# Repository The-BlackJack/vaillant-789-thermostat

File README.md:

# Vaillant 7-8-9 Smart-Home-Thermostat für Home Assistant (ESPHome)

**Smart Home für alte Vaillant-Thermen:** Ein selbst gebautes WLAN-Wandthermostat
für **Vaillant-Gasthermen ohne eBUS**. Die Heizung erscheint in **Home Assistant**
als ganz normales Thermostat, mit Raumtemperatur, Zeitplänen, Automationen,
App-Steuerung und Sprachassistent. Vor Ort gibt es ein E-Paper-Display und einen
Drehknopf. Das Thermostat
ersetzt den alten Raumregler (hier einen **calorMATIC 332**) an seinem Platz an
der Wand. Die Therme wird stufenlos über die analoge **7-8-9-Schnittstelle**
gesteuert, eingebunden ist alles per **ESPHome in Home Assistant**.

*English summary:* A DIY room thermostat for Vaillant gas boilers with the analog
7-8-9 interface (no eBUS). An ESP32-C3 drives terminal 7 through an optocoupler,
RC filter and op-amp; supply comes from terminal 8. It has an e-paper display,
a rotary encoder and an SHT3x/SHT4x sensor, runs ESPHome with PID room control,
and integrates with Home Assistant. KiCad files, Gerbers, a perfboard layout,
3D-printable enclosure (OpenSCAD) and firmware are included. Documentation is in German.

> [!WARNING]
> **Nachbau auf eigene Gefahr.** Du arbeitest an einer Gasheizung. Die
> 7-8-9-Klemmen führen Kleinspannung (ca. 24 V), trotzdem gilt:
> - Die Therme vorher stromlos schalten.
> - Nur die Klemmen des Raumreglers anfassen.
> - Bei Unsicherheit eine Fachkraft fragen.
>
> Ein Fehler in der Steuerung kann die Heizung abschalten oder heißer laufen
> lassen. Der Drehknopf an der Therme bleibt in jedem Fall die obere Grenze.
> **Projektstand:** Schaltung, Platine und Firmware sind entworfen und
> geprüft (ERC/DRC fehlerfrei, Firmware-YAML syntaktisch geprüft), aber
> **noch nicht als fertiges Gerät im Betrieb getestet.** Erfahrungen und
> Korrekturen sind willkommen (Issues / Pull Requests).

---

## Inhalt

- [Wie funktioniert die 7-8-9-Schnittstelle?](#wie-funktioniert-die-7-8-9-schnittstelle)
- [Schaltung](#schaltung)
- [Funktionen der Firmware](#funktionen-der-firmware)
- [Drei Hardware-Varianten](#drei-hardware-varianten)
- [Teile](#teile)
- [Gehäuse (3D-Druck)](#gehäuse-3d-druck)
- [Aufbau und Inbetriebnahme](#aufbau-und-inbetriebnahme)
- [Kalibrierung](#kalibrierung)
- [Ordnerstruktur](#ordnerstruktur)
- [Offene Punkte](#offene-punkte)
- [Lizenz](#lizenz)

---

## Wie funktioniert die 7-8-9-Schnittstelle?

Ältere Vaillant-Thermen (hier eine **atmoTEC VCW 194/3-C-HL**) haben drei
Klemmen für einen stetigen Raumregler:

| Klemme | Bedeutung |
| --- | --- |
| **7** | Stellsignal: Spannung bestimmt die Vorlauf-Solltemperatur |
| **8** | Versorgung für den Regler (ca. 24 V) |
| **9** | Masse |

Der Regler **zieht Klemme 7 herunter**. Je niedriger die Spannung, desto
niedriger die Vorlauftemperatur. Unter etwa 10 V ist die Heizung aus. Die Therme
nimmt immer das **Minimum** aus Klemme 7 und ihrem eigenen Drehknopf, der Knopf
ist also eine harte Obergrenze.

An meiner Therme gemessen:

| Messung | Wert |
| --- | --- |
| Klemme 8 gegen 9 | 23,6 V (unter 24 mA Last kein relevanter Abfall) |
| Klemme 7 offen (kein Regler) | 22 V |
| Klemme 7, keine Wärmeanforderung | 10,1 V |
| Klemme 7, volle Anforderung | 17,8 V → 82 °C Vorlauf (Drehknopf voll auf) |

Andere Thermen können abweichen. Deshalb gibt es in der Firmware eine
[Kalibrierung](#kalibrierung).

## Schaltung

Schaltplan als PDF: [pcb-tht/fertigung/schaltplan.pdf](pcb-tht/fertigung/schaltplan.pdf)

```
VERSORGUNG (aus Klemme 8, Masse = Klemme 9 = ESP-GND)
  Kl.8 ─►|─ D1 1N5819 ─┬─ +V (ca. 23 V) ─ C1 100µF ─ GND
                       ├─ U2 78L09 ─ +9V  (C3 am Eingang, C4 100n am Ausgang)
                       └─ R7 100Ω ─┬─ C7 220µF ─ GND
                                   └─ U4 TRACO TSR 0.5-2450 ─┬─ C8 1000µF ─ GND
                                                             └─ ESP32-C3 SuperMini „5V“
STEUERUNG KLEMME 7 (fail-safe: ESP aus → Opto aus → +9 V am Tiefpass → Klemme 7 frei)
  GPIO3 ─ R1 330Ω ─ PC817 (Anode)            PC817 Kathode, Emitter ─ GND
  PC817 Kollektor ─ R2 10k ─ +9V
  PC817 Kollektor ─ R3 100k ─┬─ LM358 IN+
                             └─ C5 4,7µF X7R (kein Elko) ─ GND
  LM358 IN− ─ R4 100k ─ GND,  IN− ─ R5 120k ─ OUT   → Verstärkung 2,2
  Kl.7 ─ R6 220Ω ─►|─ LM358 OUT   (D2 1N4148, Kathode zum OPV)
```

- **PWM und Optokoppler:** Der ESP erzeugt ein PWM-Signal (500 Hz). Der
  Optokoppler zieht damit einen 9-V-Pegel taktweise auf Masse.
- **Glättung:** Der RC-Tiefpass macht daraus eine Gleichspannung von 0–9 V.
- **OPV:** Er verstärkt diese Spannung mit Faktor 2,2 auf 0–19,8 V und zieht
  Klemme 7 über die Diode auf diesen Wert herunter. Hochziehen kann er die
  Klemme nicht.
- **Fail-safe:** Fällt der ESP aus, sperrt der Optokoppler. Klemme 7 bleibt dann
  bei etwa 20 V, und die Therme heizt nach ihrem eigenen Drehknopf.
- **Arbeitsbereich:** 10,1–17,8 V an Klemme 7 entsprechen etwa 48–87 % PWM.
  Im Mittel braucht die Schaltung 12–15 mA aus Klemme 8.

**Peripherie (3,3 V vom ESP):**

| Teil | Anschlüsse |
| --- | --- |
| E-Paper Waveshare 2,9" V2 | DIN GPIO6, CLK GPIO4, CS GPIO7, DC GPIO5, RST GPIO10, BUSY GPIO1 |
| Sensor SHT31-D (oder SHT40) | SDA GPIO8, SCL GPIO9 |
| Drehgeber EC11 mit Taster | A GPIO21, B GPIO20, Taster GPIO0 |

## Funktionen der Firmware

Datei: [vaillant-789.yaml](vaillant-789.yaml) (ESPHome, ESP-IDF)

- **PID-Raumregelung:** In Home Assistant erscheint ein normales Thermostat.
  Der Wärmebedarf (0–100 %) wird auf einen einstellbaren Vorlaufbereich
  umgerechnet.
- **Betriebsarten:**
  - Aus
  - Raumregelung
  - Vorlauf manuell
  - Kalibrierung (PWM-Pegel direkt vorgeben)
- **Notbetrieb:** Fällt der Raumsensor aus, wird eine feste Vorlauftemperatur gefahren.
- **E-Paper-Anzeige:**
  - Raumtemperatur und Soll-Wert
  - Vorlauf-Soll und Wärmebedarf (bei „Vorlauf manuell“ und Kalibrierung
    stattdessen der tatsächliche PWM-Pegel)
  - Status und WLAN

  Simulation der Anzeige in sechs Zuständen, erzeugt mit
  [tools/display_sim.py](tools/display_sim.py) (gleiche Koordinaten und
  Schriften wie in der YAML, prüft Überstände).
- **Drehgeber:**
  - Drehen: Soll-Temperatur in 0,5-°C-Schritten
  - Drücken: Heizung ein/aus
- **Kalibrierung über Home Assistant:**
  - Spannung bei 50 % / 85 % PWM
  - Kennlinie Vorlauf ↔ Spannung (zwei Punkte)
  - Temperatur-Offset

Für eigene Zugangsdaten [secrets.example.yaml](secrets.example.yaml) nach
`secrets.yaml` kopieren und ausfüllen. Den Sensor-Typ (SHT31-D: `sht3xd`,
SHT40: `sht4x`) passt du in der YAML an.

## Drei Hardware-Varianten

Die Schaltung ist in allen drei Varianten gleich. Du kannst dir aussuchen, wie
du sie aufbaust.

| Variante | Ordner | Beschreibung |
| --- | --- | --- |
| **A – Platine zum Selbstlöten (empfohlen)** | [`pcb-tht/`](pcb-tht/) | Nur die Leiterplatte bei JLCPCB o. ä. fertigen lassen (Gerber-ZIP liegt bei). Alle Bauteile bedrahtet, nur zwei Kondensatoren als SMD 1210 mit Handlöt-Pads. |
| B – Platine mit SMD-Bestückung | [`pcb/`](pcb/) | Komplett bei JLCPCB bestückt (BOM/CPL im JLCPCB-Format). Bequemer, aber deutlich teurer. |
| C – Lochraster | [`lochraster/`](lochraster/) | 70 × 50 mm Lochrasterplatine mit Bestückungs- und Verdrahtungsplan. Ein Skript prüft alle Verbindungen. |

| THT-Platine (oben) | SMD-Variante | Lochraster (Lötseite) |
| --- | --- | --- |
|  |  |  |

**Zu allen Platinen:**
- **Format:** 70 × 50 mm, 2 Lagen.
- **Anschluss Therme:** Schraubklemme 7-8-9 am rechten Rand.
- **ESP:** Der ESP32-C3 SuperMini steckt in zwei Buchsenleisten, mit der Antenne nach oben über einer kupferfreien Zone.
- **Erzeugung:** Die KiCad-Projekte werden per Python-Skript aus einer
  gemeinsamen Netzliste erzeugt (`tools/design.py`), inklusive eines kleinen
  eigenen Autorouters. Du kannst die Dateien aber auch ganz normal in KiCad 10
  öffnen und bearbeiten.

## Teile

Alle Teile sind bei **Reichelt** erhältlich, der ESP32-C3 SuperMini zum
Beispiel bei Blinkyparts oder AliExpress. Stückliste mit Artikelnummern und
Links: [lochraster/README.md → Einkaufsliste](lochraster/README.md#einkaufsliste).
Für Variante A brauchst du die Lochrasterplatine und den Silberdraht daraus nicht.

Kosten (Stand Ende 2026): etwa 55 € bei Reichelt, davon rund 40 € für Display,
Sensor und Drehgeber. Dazu kommen ca. 5 € für den ESP und ein paar Euro für 5
Leiterplatten.

## Gehäuse (3D-Druck)

- **Modell:** Parametrisch in OpenSCAD:
  [vaillant-789-gehaeuse.scad](vaillant-789-gehaeuse.scad), 150 × 100 × 36 mm.
  Fertige STLs liegen in [`druck/`](druck/):
  - Rückplatte, wird an die Wand geschraubt (Langlöcher an den Positionen der alten calorMATIC-Halterung)
  - Frontgehäuse mit Displayfenster, belüfteter Sensorkammer und Lüftung oben
  - Drehknopf für die EC11-Achse (rund mit Schlitz oder D-Achse, umschaltbar)
- **Verschraubung:** ruthex-Gewindeeinsätze,
  M2 für die Platine und M3 für Front und Rückplatte. Die Maße sind oben in der
  `.scad` als Parameter einstellbar.
- **Material:** PETG oder ASA. PLA wird an der Wand in Heizungsnähe weich.
  Gute Werte sind 0,2 mm Schichthöhe, 3 Wände und 20 % Füllung.
- **Passform:** Die Platine ist mit den hohen Bauteilen gegen das Gehäuse
  geprüft ([Seitenansicht](druck/passform-seite.png)).
- **Maße:** Siehe [gehaeuse-massbild.png](gehaeuse-massbild.png). Wer eine
  andere Halterung hat, ändert `screw_ur` und `screw_ll` in der `.scad`.

## Aufbau und Inbetriebnahme

1. **Platine bestücken:** Die Hinweise zur Einbaurichtung stehen in
   [pcb-tht/README.md](pcb-tht/README.md) bzw. [lochraster/README.md](lochraster/README.md).
2. **Ohne Therme testen:** Etwa 24 V an Klemme 8/9 anlegen (Labornetzteil, Strom
   auf 100 mA begrenzen) und die Spannungen messen:
   - **+V:** ca. 23 V
   - **+9V:** 9 V
   - **5V am ESP:** 5 V
3. **ESP flashen:** `vaillant-789.yaml` im ESPHome Device Builder kompilieren
   und per USB flashen. Danach geht es auch per OTA.
4. **Ausgang prüfen, noch ohne Therme:** Klemme 7 über einen Widerstand von
   etwa 10 kΩ an 22 V hängen. In der Betriebsart „Pegel manuell“ die Spannung
   an Klemme 7 bei verschiedenen PWM-Pegeln messen.
5. **An die Therme anschließen:** Therme stromlos schalten, den alten Regler
   abklemmen und 7-8-9 an die Schraubklemme anschließen.

## Kalibrierung

Alle Werte stellst du in Home Assistant ein. Sie werden dauerhaft gespeichert.

1. **PWM-Kennlinie:** Betriebsart „Pegel manuell (Kalibrierung)“ wählen. PWM
   auf 50 % und auf 85 % stellen und jeweils die Spannung an Klemme 7 messen.
   Die Werte trägst du unter „Spannung bei Pegel 50 %/85 %“ ein.
2. **Vorlauf-Kennlinie:** Betriebsart „Vorlauf manuell“ wählen. Für einen
   niedrigen und einen hohen Vorlauf jeweils die Spannung und den Vorlauf an der
   Therme ablesen und als unteren und oberen Kennlinienpunkt eintragen.
3. **„Heizung aus“:** Die Spannung, bei der die Therme sicher aus ist, etwa
   0,5 V unter der gemessenen Schwelle.
4. **Temperatur-Offset:** Gleicht die Eigenerwärmung im Gehäuse aus. Dazu mit
   einem Referenzthermometer vergleichen.

## Ordnerstruktur

```
vaillant-789.yaml             ESPHome-Firmware
secrets.example.yaml          Vorlage für die Zugangsdaten
vaillant-789-gehaeuse.scad    Gehäuse (OpenSCAD)
druck/                        STL-Dateien und Ansichten
gehaeuse-massbild.png         Maßbild Gehäuse
display-sim.png               Simulation der E-Paper-Anzeige
tools/display_sim.py          erzeugt display-sim.png aus dem Display-Code
pcb-tht/                      Variante A: KiCad-Projekt THT, Gerber, Renders, Generator-Skripte
pcb/                          Variante B: KiCad-Projekt SMD (JLCPCB-Bestückung), BOM/CPL
lochraster/                   Variante C: Lochraster-Layout, Verdrahtungsliste, Einkaufsliste
Einkaufsliste.md              Bestellliste für Variante B
```

## Offene Punkte

- **ESP-Reihenabstand:** Den Abstand der beiden Pinreihen des ESP32-C3
  SuperMini (15,24 mm angenommen) am eigenen Modul nachmessen. Es gibt Klone mit
  abweichendem Abstand.
- **Firmware:** Kompiliert mit ESPHome 2026.11.0 und auf einem ESP32-C3
  SuperMini getestet (WLAN, Home-Assistant-API). Display, Sensor und Drehgeber
  sind noch nicht angeschlossen; offen sind `model: 2.90inv2` vs.
  `2.90inv2-r2` beim Display und `resolution` beim Drehgeber.
- **WLAN beim SuperMini:** Viele Module verbinden sich bei voller
  Sendeleistung nicht („Auth Expired“). Die YAML setzt deshalb
  `output_power: 8.5dB`.
- **Kalibrierung:** Der untere Kennlinienpunkt (ca. 35 °C) muss am fertigen
  Gerät bestimmt werden.
- **Display-Höhe:** Den Abstand zwischen Display-Rückseite und dem höchsten
  Elko (ca. 4 mm) am echten Display prüfen.

## Lizenz

[MIT](LICENSE). Nutzung, Nachbau und Änderung sind ausdrücklich erwünscht. Die
KiCad-Bibliotheksteile unterliegen der KiCad-Bibliothekslizenz (CC-BY-SA 4.0
mit Ausnahme für erzeugte Platinen).

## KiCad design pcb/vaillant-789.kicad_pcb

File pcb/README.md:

# Platine Vaillant 7-8-9 Thermostat (KiCad 10)

70 × 50 mm, 2 Lagen, 1,6 mm, 4 × M2-Löcher im Raster 65 × 45 mm.
ERC und DRC (mit Schaltplan-Parität) laufen ohne Fehler und Warnungen durch.

## Bestellen bei JLCPCB

1. `fertigung/vaillant-789-gerber.zip` hochladen (2 Lagen, 1,6 mm, HASL, Farbe nach Wunsch).
2. „PCB Assembly“ → **Top Side** → `fertigung/BOM-JLCPCB.csv` und `fertigung/CPL-JLCPCB.csv`.
3. **In der Bestückungsvorschau jedes Teil auf Lage und Polarität prüfen.** Die
   Drehwinkel stammen direkt aus KiCad. Bei JLC kommt es öfter vor, dass sie
   bei einzelnen Gehäusen um 90° oder 180° versetzt erscheinen. Dann im Viewer
   drehen. Besonders prüfen:
   - U3 LM358 – Punkt = Pin 1 oben links
   - U1 EL817 – Pin 1 oben links
   - U2 78M09 – Kühlfahne rechts
   - C1, C7, C8 – Elkos, „+“-Markierung
   - D1, D2 – Kathodenstrich

## Abweichungen von der Schaltung in CLAUDE.md (gleiche Funktion)

| Teil | Vorgabe | Platine | Grund |
| --- | --- | --- | --- |
| U2 | 78L09 | **CJ78M09 (DPAK, C9071)** | Einen 78L09 im SMD-Gehäuse hat JLCPCB praktisch nicht auf Lager. Pinbelegung und Funktion sind gleich, die Ruhestromaufnahme ist etwas höher (ca. 4,6 mA statt ca. 3 mA). |
| C3 | 330 nF | **1 µF/50 V (0805)** | Basic-Teil mit ausreichender Spannungsfestigkeit, mehr Kapazität schadet nicht |
| R7 | 100 Ω 0,5 W | **100 Ω 2 W (2512)** | Mehr Reserve; es gibt bei JLC keinen 0,5-W-Typ, der auf Lager ist |
| C8 | 1000 µF/10 V | **1000 µF/16 V SMD (10 × 10 mm)** | auf Lager, 10,2 mm hoch |
| U1 | PC817 | **EL817S1(C)** | gleicher Typ mit gleicher Pinbelegung; ein PC817 als Basic-Teil ist nicht auf Lager |

## Selbst einlöten (THT)

Siehe `fertigung/Teile-selbst-loeten-v2.csv` und `../Einkaufsliste.md`:

- 2 × Buchsenleiste 1×8 (RM 2,54) für den ESP32-C3 SuperMini, USB nach unten, Antenne zur Platinenoberkante.
- TRACO TSR 0.5-2450
- Schraubklemme RM 5,08: oben Klemme 7, Mitte 8, unten 9; die Kabel kommen von rechts.
- Gewinkelte Stiftleisten RM 2,54 (von einer 1×40-Leiste abbrechen). Pin 1 ist jeweils rechts.
  - **J2 Display (9 Pins):** VCC, GND, DIN, CLK, CS, DC, RST, BUSY, PWR. Das beiliegende Waveshare-Kabel wird direkt aufgesteckt. PWR (nur bei neueren Modulen) liegt auf 3,3 V.
  - **J3 Sensor (4 Pins, unten links):** V = 3,3 V, G = GND, D = SDA, C = SCL.
  - **J4 Drehgeber (5 Pins, unten Mitte):** A, G, B, S (Taster), G.

  J3 und J4 zeigen über die Unterkante hinaus. Die Dupont-Stecker sitzen dann
  neben der Sensorkammer, links davon.

**Vor dem Bestellen nachmessen:** Der Footprint geht beim SuperMini von einem
Reihenabstand von 15,24 mm aus, mit dieser Belegung von unten (USB) nach oben:
links 5V-GND-3V3-4-3-2-1-0, rechts 5-6-7-8-9-10-20-21. Wenn dein Modul
anders aussieht, `ESP_LEFT`/`ESP_RIGHT` und den Abstand in `tools/gen_sch.py`
anpassen und neu erzeugen.

Verbindung zu Sensor und Drehgeber: Jumper-Kabel Buchse–Buchse verwenden. Am
Drehgeber die eine Buchse abschneiden und die Litze direkt anlöten.

## Neu erzeugen

Alles wird per Skript aus `tools/design.py` erzeugt: Netzliste, Bauteile,
Positionen und LCSC-Nummern. Der Router ist ein eigener A*-Router auf einem
0,1-mm-Raster; Freerouting ist nicht nötig.

```powershell
& "C:\Program Files\KiCad\10.0\bin\python.exe" tools\gen_sch.py
```
```powershell
& "C:\Program Files\KiCad\10.0\bin\python.exe" tools\gen_pcb.py
```
```powershell
& "C:\Program Files\KiCad\10.0\bin\kicad-cli.exe" pcb drc --severity-all --schematic-parity vaillant-789.kicad_pcb
```
```powershell
& "C:\Program Files\KiCad\10.0\bin\python.exe" tools\export.py
```

Achtung: `gen_pcb.py` überschreibt die `.kicad_pcb`-Datei. Wer in KiCad von
Hand nachbessert, sollte das Skript danach nicht mehr laufen lassen.

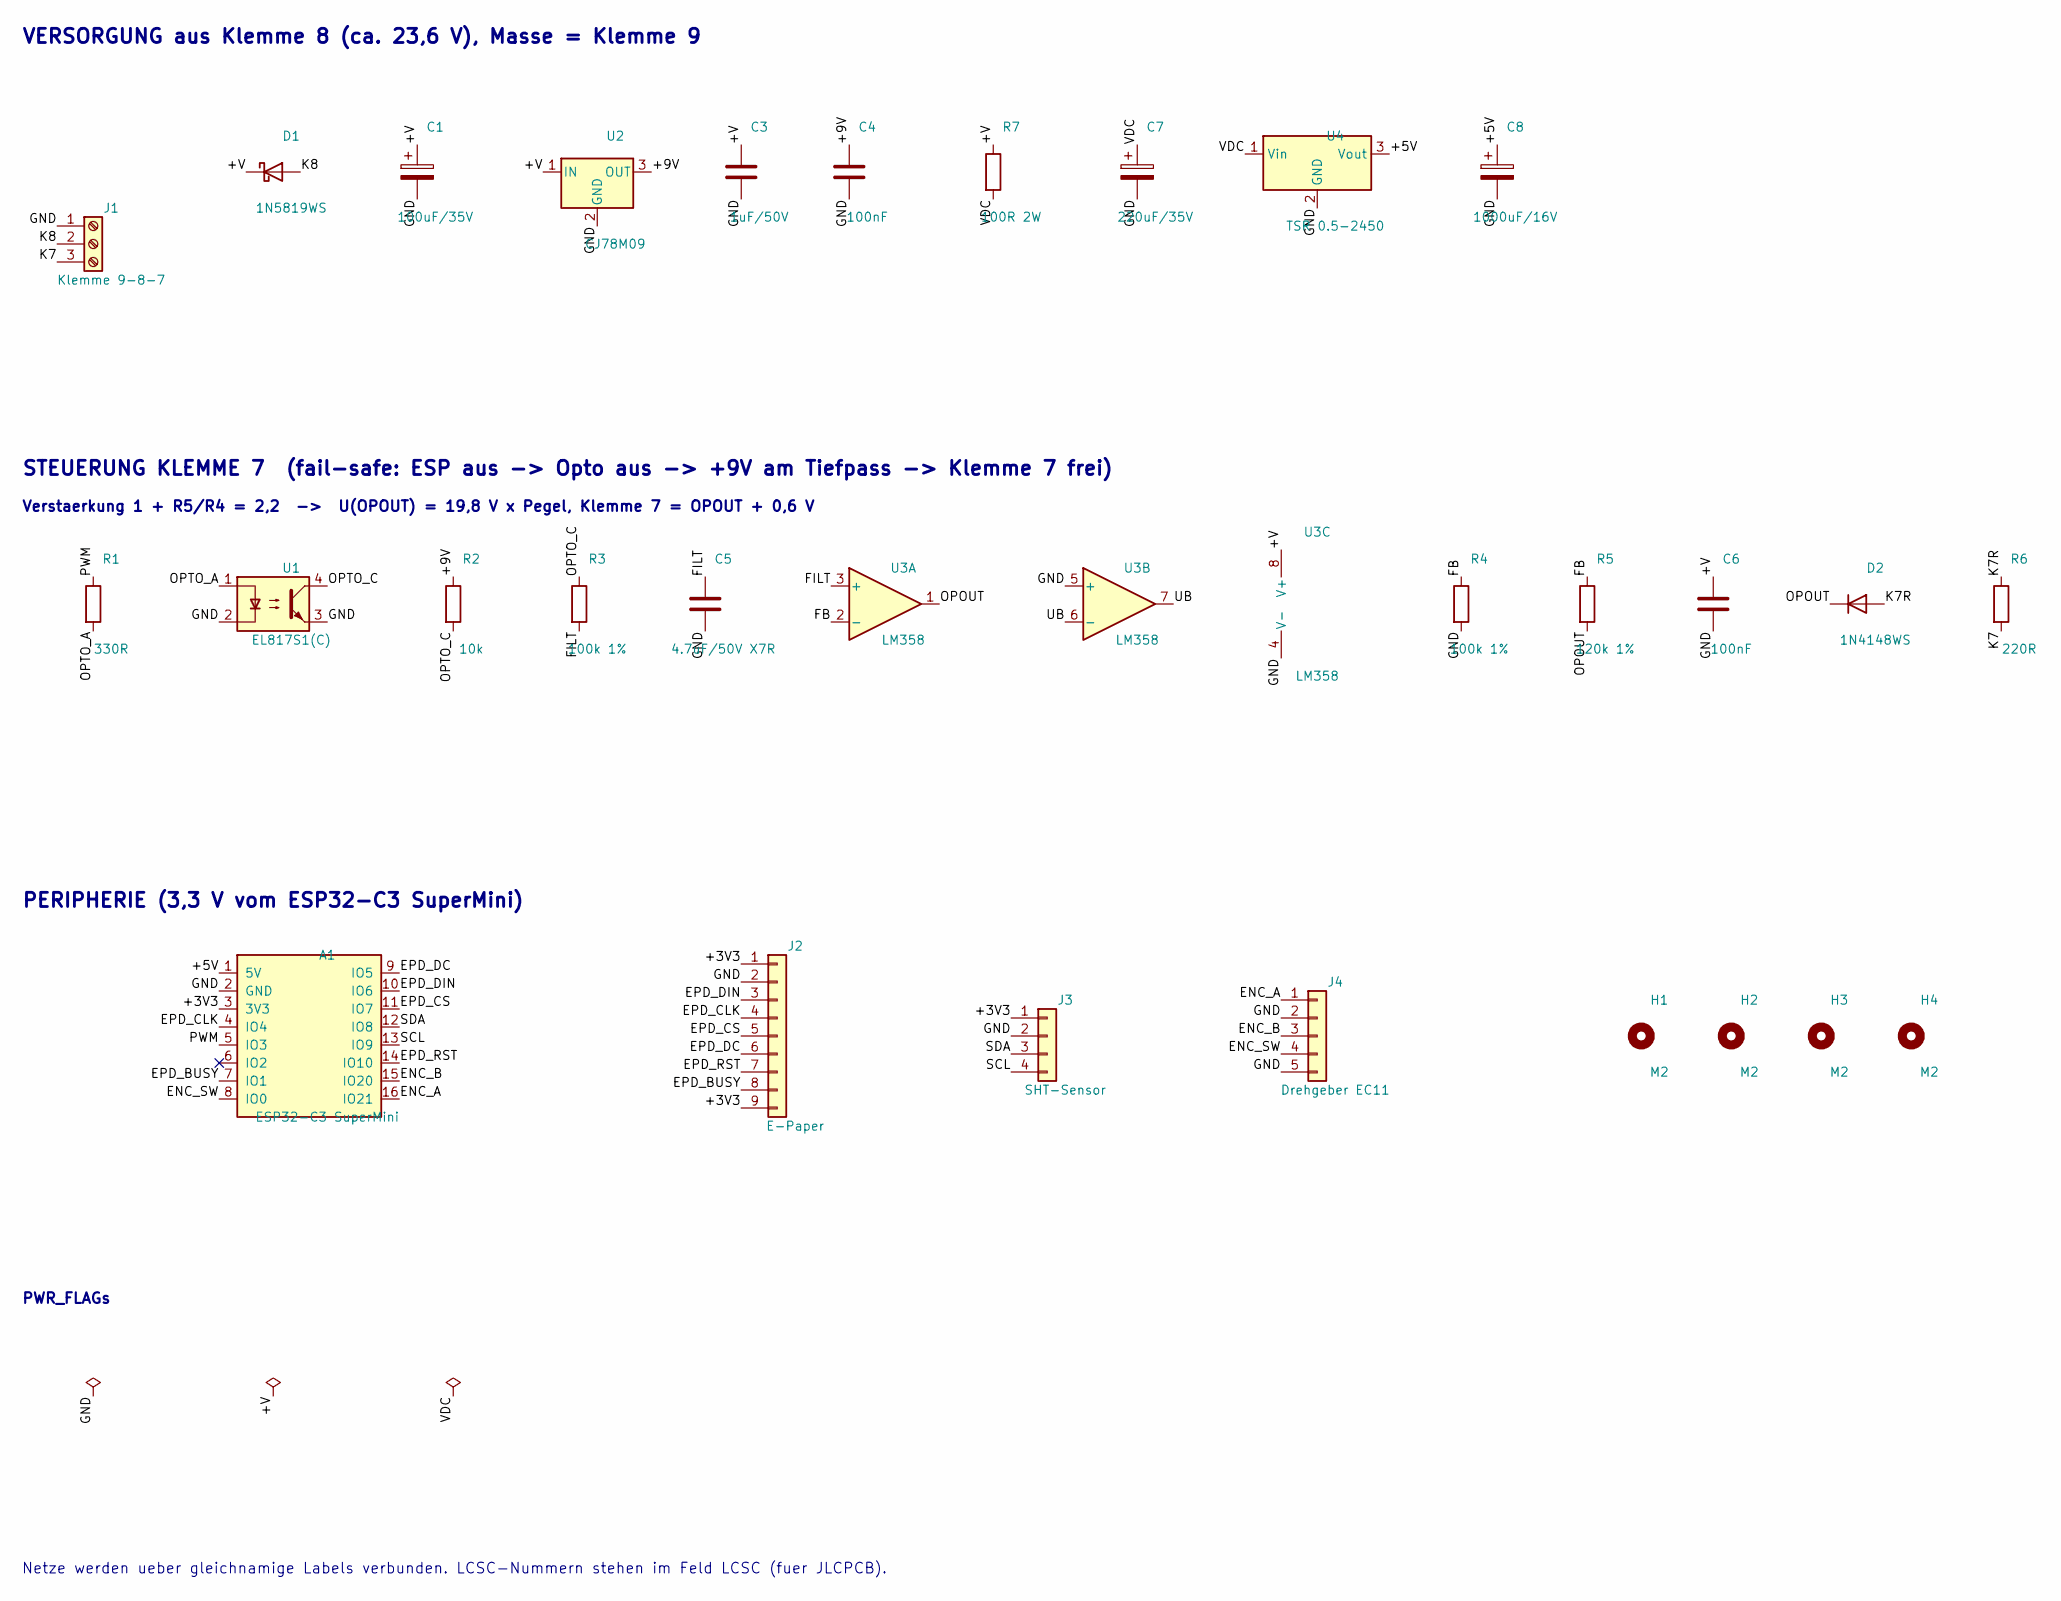
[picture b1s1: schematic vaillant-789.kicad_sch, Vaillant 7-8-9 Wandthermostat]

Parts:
A1: ESP32-C3 SuperMini; ESP32-C3_SuperMini_Socket; MPN ESP32-C3 SuperMini + 2x Buchsenleiste 1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
C1: 100uF/35V; CP_Elec_6.3x7.7; MPN RVT100UF35V67RV0034; LCSC C2836442
C3: 1uF/50V; C_0805_2012Metric; MPN CL21B105KBFNNNE; LCSC C28323
C4, C6: 100nF; C_0603_1608Metric; MPN CC0603KRX7R9BB104; LCSC C14663
C5: 4.7uF/50V X7R; C_1206_3216Metric; MPN 1206B475K500NT; LCSC C29823
C7: 220uF/35V; CP_Elec_6.3x7.7; MPN 189RV0019; LCSC C7471881
C8: 1000uF/16V; CP_Elec_10x10; MPN RVT1C102M1010; LCSC C3359
D1: 1N5819WS; D_SOD-323; MPN 1N5819WS; LCSC C191023
D2: 1N4148WS; D_SOD-323; MPN 1N4148WS; LCSC C2128
H1, H2, H3, H4: M2; MountingHole_2.2mm_M2
J1: Klemme 9-8-7; TerminalBlock_Phoenix_MKDS-1,5-3-5.08_1x03_P5.08mm_Horizont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; MPN Phoenix MKDS 1,5/3-5,08 (oder kompatibe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
J2: E-Paper; PinHeader_1x09_P2.54mm_Horizontal; MPN Stiftleiste 1x9 gewinkelt RM 2,54 (Pin 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
J3: SHT-Sensor; PinHeader_1x04_P2.54mm_Horizontal; MPN Stiftleiste 1x4 gewinkelt RM 2,54
J4: Drehgeber EC11; PinHeader_1x05_P2.54mm_Horizontal; MPN Stiftleiste 1x5 gewinkelt RM 2,54
R1: 330R; R_0603_1608Metric; MPN 0603WAF3300T5E; LCSC C23138
R2: 10k; R_0603_1608Metric; MPN 0603WAF1002T5E; LCSC C25804
R3, R4: 100k 1%; R_0603_1608Metric; MPN 0603WAF1003T5E; LCSC C25803
R5: 120k 1%; R_0603_1608Metric; MPN 0603WAF1203T5E; LCSC C25808
R6: 220R; R_0603_1608Metric; MPN 0603WAF2200T5E; LCSC C22962
R7: 100R 2W; R_2512_6332Metric; MPN CRH2512F100RE04Z; LCSC C175280
U1: EL817S1(C); SMDIP-4_W9.53mm; MPN EL817S1(C)(TU)-F; LCSC C2912100
U2: CJ78M09; TO-252-2; MPN CJ78M09; LCSC C9071
U3: LM358; SOIC-8_3.9x4.9mm_P1.27mm; MPN LM358DR2G; LCSC C7950
U4: TSR 0.5-2450; Converter_DCDC_TRACO_TSR0.5-24xx_TSR0.5-24xxx_THT; MPN TRACO TSR 0.5-2450

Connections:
/+3V3: A1.3 (3V3), J2.1, J2.9, J3.1
/+5V: A1.1 (5V), C8.1, U4.3 (Vout)
/+9V: C4.1, R2.1, U2.3 (OUT)
/+V: C1.1, C3.1, C6.1, D1.1 (K), R7.1, U2.1 (IN), U3.8 (V+)
/ENC_A: A1.16 (IO21), J4.1
/ENC_B: A1.15 (IO20), J4.3
/ENC_SW: A1.8 (IO0), J4.4
/EPD_BUSY: A1.7 (IO1), J2.8
/EPD_CLK: A1.4 (IO4), J2.4
/EPD_CS: A1.11 (IO7), J2.5
/EPD_DC: A1.9 (IO5), J2.6
/EPD_DIN: A1.10 (IO6), J2.3
/EPD_RST: A1.14 (IO10), J2.7
/FB: R4.1, R5.1, U3.2 (-)
/FILT: C5.1, R3.2, U3.3 (+)
/GND: A1.2 (GND), C1.2, C3.2, C4.2, C5.2, C6.2, C7.2, C8.2, J1.1, J2.2, J3.2, J4.2, J4.5, R4.2, U1.2, U1.3, U2.2 (GND), U3.4 (V-), U3.5 (+), U4.2 (GND)
/K7: J1.3, R6.2
/K7R: D2.2 (A), R6.1
/K8: D1.2 (A), J1.2
/OPOUT: D2.1 (K), R5.2, U3.1
/OPTO_A: R1.2, U1.1
/OPTO_C: R2.2, R3.1, U1.4
/PWM: A1.5 (IO3), R1.1
/SCL: A1.13 (IO9), J3.4
/SDA: A1.12 (IO8), J3.3
/UB: U3.6 (-), U3.7
/VDC: C7.1, R7.2, U4.1 (Vin)

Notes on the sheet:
VERSORGUNG aus Klemme 8 (ca. 23,6 V), Masse = Klemme 9
STEUERUNG KLEMME 7 (fail-safe: ESP aus -> Opto aus -> +9V am Tiefpass -> Klemme 7 frei)
Verstaerkung 1 + R5/R4 = 2,2 -> U(OPOUT) = 19,8 V x Pegel, Klemme 7 = OPOUT + 0,6 V
PERIPHERIE (3,3 V vom ESP32-C3 SuperMini)
PWR_FLAGs
Netze werden ueber gleichnamige Labels verbunden. LCSC-Nummern stehen im Feld LCSC (fuer JLCPCB).

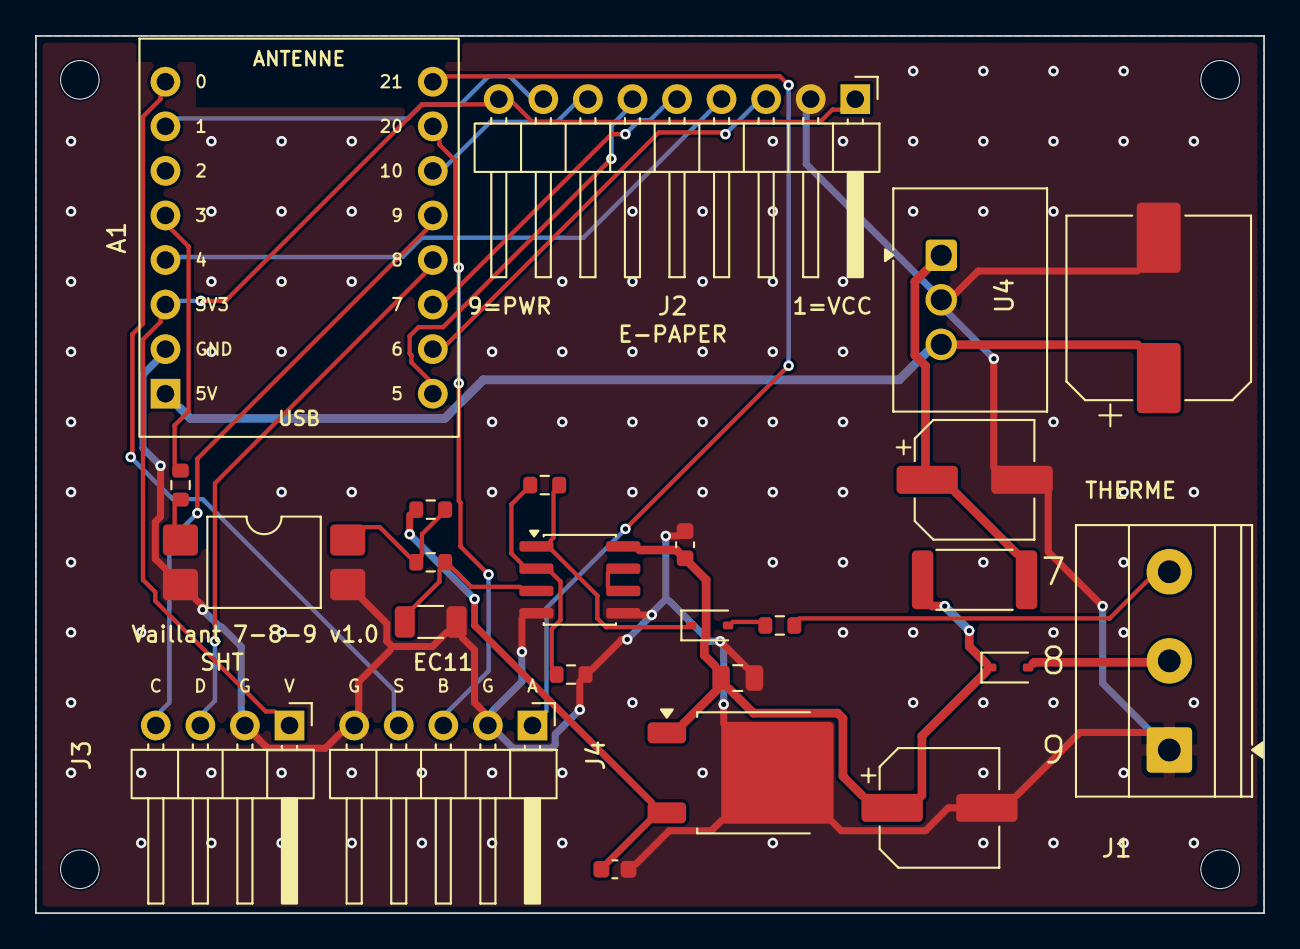
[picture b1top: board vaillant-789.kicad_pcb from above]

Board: 2 copper layers, 70.0 x 50.0 mm, 29 parts (0 on the bottom side), 27 nets.

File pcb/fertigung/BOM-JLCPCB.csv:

Comment,Designator,Footprint,JLCPCB Part #
100uF/35V,C1,CP_Elec_6.3x7.7,C2836442
1uF/50V,C3,C_0805_2012Metric,C28323
100nF,"C4,C6",C_0603_1608Metric,C14663
4.7uF/50V X7R,C5,C_1206_3216Metric,C29823
220uF/35V,C7,CP_Elec_6.3x7.7,C7471881
1000uF/16V,C8,CP_Elec_10x10,C3359
1N5819WS,D1,D_SOD-323,C191023
1N4148WS,D2,D_SOD-323,C2128
330R,R1,R_0603_1608Metric,C23138
10k,R2,R_0603_1608Metric,C25804
100k 1%,"R3,R4",R_0603_1608Metric,C25803
120k 1%,R5,R_0603_1608Metric,C25808
220R,R6,R_0603_1608Metric,C22962
100R 2W,R7,R_2512_6332Metric,C175280
EL817S1(C),U1,SMDIP-4_W9.53mm,C2912100
CJ78M09,U2,TO-252-2,C9071
LM358,U3,SOIC-8_3.9x4.9mm_P1.27mm,C7950

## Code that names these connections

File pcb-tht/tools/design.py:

# -*- coding: utf-8 -*-
"""THT-Variante: JLCPCB fertigt nur die Leiterplatte, alle Teile werden selbst eingeloetet
(Reichelt-Teile wie in lochraster/README.md).

"pos" = (x, y, Drehung) in mm, Ursprung oben links auf der Platine, y nach unten.
Bei Zweibeinern liegt "pos" auf Pad 1. Montageloecher sitzen auf den Eckloechern des
Lochrasters ("grid"), damit das Gehaeuse (.scad) fuer beide Varianten passt.
"""

PROJECT = "vaillant-789"
GX0, GY0, GP = 1.98, 2.14, 2.54


def G(c, r):
    return (GX0 + GP * c, GY0 + GP * r)


R10 = "Resistor_THT:R_Axial_DIN0207_L6.3mm_D2.5mm_P10.16mm_Horizontal"
CAP1210 = "Capacitor_SMD:C_1210_3225Metric_Pad1.33x2.70mm_HandSolder"
DISC = "Capacitor_THT:C_Disc_D4.3mm_W1.9mm_P5.00mm"

PARTS = [
    # --- Versorgung -------------------------------------------------------
    dict(ref="J1", sym="Connector:Screw_Terminal_01x03", value="Klemme 9-8-7",
         fp="TerminalBlock_Phoenix:TerminalBlock_Phoenix_MKDS-1,5-3-5.08_1x03_P5.08mm_Horizontal",
         pins={"1": "GND", "2": "K8", "3": "K7"}, pos=(62.94, 40.24, 90), sch=(30.48, 50.8), mpn="MKDS 1,5 3 5,08"),
    dict(ref="D1", sym="Device:D_Schottky", value="1N5819", fp="Diode_THT:D_DO-41_SOD81_P10.16mm_Horizontal",
         pins={"1": "+V", "2": "K8"}, pos=(54.5, 32.5, 270), sch=(55.88, 40.64), mpn="1N 5819"),
    dict(ref="C1", sym="Device:C_Polarized", value="100uF/35V", fp="Capacitor_THT:CP_Radial_D6.3mm_P2.50mm",
         pins={"1": "+V", "2": "GND"}, pos=(47.25, 37.5, 0), sch=(76.2, 40.64), mpn="RAD 105 100/35"),
    dict(ref="U2", sym="Regulator_Linear:L78L09_TO92", value="78L09", fp="Package_TO_SOT_THT:TO-92_Inline_Wide",
         pins={"1": "+9V", "2": "GND", "3": "+V"}, pos=(34.0, 43.5, 0), sch=(101.6, 40.64), mpn="µA 78L09"),
    dict(ref="C3", sym="Device:C", value="4.7uF/50V X7R 1210", fp=CAP1210,
         pins={"1": "+V", "2": "GND"}, pos=(42.5, 43.5, 90), sch=(121.92, 40.64), mpn="KEM X7R1210 4,7U"),
    dict(ref="C4", sym="Device:C", value="100nF", fp=DISC,
         pins={"1": "+9V", "2": "GND"}, pos=(34.0, 47.6, 0), sch=(137.16, 40.64), mpn="X7R-5 100N"),
    dict(ref="R7", sym="Device:R", value="100R 0,6W", fp=R10,
         pins={"1": "VDC", "2": "+V"}, pos=(48.5, 7.5, 270), sch=(157.48, 40.64), mpn="METALL 100"),
    dict(ref="C7", sym="Device:C_Polarized", value="220uF/35V", fp="Capacitor_THT:CP_Radial_D8.0mm_P3.50mm",
         pins={"1": "VDC", "2": "GND"}, pos=(40.75, 9.8, 0), sch=(177.8, 40.64), mpn="RAD FC 220/35"),
    dict(ref="U4", sym="Converter_DCDC:TSR_1-2450", value="TSR 0.5-2450",
         fp="Converter_DCDC:Converter_DCDC_TRACO_TSR0.5-24xx_TSR0.5-24xxx_THT",
         pins={"1": "VDC", "2": "GND", "3": "+5V"}, pos=(55.86, 4.68, 0), sch=(203.2, 40.64), mpn="TSR 0.5-2450"),
    dict(ref="C8", sym="Device:C_Polarized", value="1000uF/10V", fp="Capacitor_THT:CP_Radial_D10.0mm_P5.00mm",
         pins={"1": "+5V", "2": "GND"}, pos=(61.0, 19.5, 0), sch=(228.6, 40.64), mpn="FC-A 1000U 10A"),
    # --- Steuerung Klemme 7 ---------------------------------------------------
    dict(ref="R1", sym="Device:R", value="330R", fp=R10,
         pins={"1": "OPTO_A", "2": "PWM"}, pos=(7.0, 29.6, 0), sch=(30.48, 101.6), mpn="METALL 330"),
    dict(ref="U1", sym="Isolator:PC817", value="PC817", fp="Package_DIP:DIP-4_W7.62mm",
         pins={"1": "OPTO_A", "2": "GND", "3": "GND", "4": "OPTO_C"}, pos=(8.0, 33.0, 0),
         sch=(55.88, 101.6), mpn="PC817X1NSZ1B"),
    dict(ref="R2", sym="Device:R", value="10k", fp=R10,
         pins={"1": "OPTO_C", "2": "+9V"}, pos=(15.0, 43.0, 0), sch=(81.28, 101.6), mpn="METALL 10,0K"),
    dict(ref="R3", sym="Device:R", value="100k 1%", fp=R10,
         pins={"1": "OPTO_C", "2": "FILT"}, pos=(15.0, 39.5, 0), sch=(99.06, 101.6), mpn="METALL 100K"),
    dict(ref="C5", sym="Device:C", value="4.7uF/50V X7R 1210", fp=CAP1210,
         pins={"1": "FILT", "2": "GND"}, pos=(29.5, 41.5, 0), sch=(116.84, 101.6), mpn="KEM X7R1210 4,7U"),
    dict(ref="U3", sym="Amplifier_Operational:LM358", value="LM358", fp="Package_DIP:DIP-8_W7.62mm",
         pins={"3": "FILT", "2": "FB", "1": "OPOUT", "5": "GND", "6": "UB", "7": "UB", "8": "+V", "4": "GND"},
         pos=(32.0, 30.0, 0), units={1: (142.24, 101.6), 2: (175.26, 101.6), 3: (200.66, 101.6)}, sch=None,
         mpn="LM 358 DIP + Fassung GS 8"),
    dict(ref="R4", sym="Device:R", value="100k 1%", fp="Resistor_THT:R_Axial_DIN0207_L6.3mm_D2.5mm_P5.08mm_Vertical",
         pins={"1": "FB", "2": "GND"}, pos=(28.0, 31.27, 270), sch=(223.52, 101.6), mpn="METALL 100K"),
    dict(ref="R5", sym="Device:R", value="120k 1%", fp=R10,
         pins={"1": "FB", "2": "OPOUT"}, pos=(29.5, 26.5, 0), sch=(241.3, 101.6), mpn="METALL 120K"),
    dict(ref="C6", sym="Device:C", value="100nF", fp=DISC,
         pins={"1": "+V", "2": "GND"}, pos=(43.0, 30.0, 270), sch=(259.08, 101.6), mpn="X7R-5 100N"),
    dict(ref="D2", sym="Device:D", value="1N4148", fp="Diode_THT:D_DO-35_SOD27_P10.16mm_Horizontal",
         pins={"1": "OPOUT", "2": "K7R"}, pos=(31.0, 23.5, 0), sch=(279.4, 101.6), mpn="1N 4148"),
    dict(ref="R6", sym="Device:R", value="220R", fp=R10,
         pins={"1": "K7R", "2": "K7"}, pos=(43.5, 23.5, 0), sch=(299.72, 101.6), mpn="METALL 220"),
    # --- Peripherie ------------------------------------------------------------
    dict(ref="A1", sym="vaillant:ESP32-C3_SuperMini", value="ESP32-C3 SuperMini",
         fp="vaillant:ESP32-C3_SuperMini_Socket",
         pins={"1": "+5V", "2": "GND", "3": "+3V3", "4": "EPD_CLK", "5": "PWM", "6": None,
               "7": "EPD_BUSY", "8": "ENC_SW", "9": "EPD_DC", "10": "EPD_DIN", "11": "EPD_CS",
               "12": "SDA", "13": "SCL", "14": "EPD_RST", "15": "ENC_B", "16": "ENC_A"},
         pos=(14.68, 16.11, 0), sch=(60.96, 162.56),
         mpn="ESP32-C3 SuperMini + 2x Buchsenleiste FIS BL1 08 Z"),
    # Kabel-Loetpunkte (Litzen direkt einloeten oder Stiftleiste)
    dict(ref="J2", sym="Connector_Generic:Conn_01x09", value="Display",
         fp="Connector_PinHeader_2.54mm:PinHeader_1x09_P2.54mm_Vertical",
         pins={"1": "+3V3", "2": "GND", "3": "EPD_DIN", "4": "EPD_CLK", "5": "EPD_CS", "6": "EPD_DC",
               "7": "EPD_RST", "8": "EPD_BUSY", "9": "+3V3"}, pos=(24.0, 2.14, 90), sch=(127.0, 162.56),
         mpn="Display-Kabel einloeten (Pin 9 = PWR neuerer Module)",
         labels=["VCC", "GND", "DIN", "CLK", "CS", "DC", "RST", "BSY", "PWR"]),
    dict(ref="J3", sym="Connector_Generic:Conn_01x04", value="Sensor",
         fp="Connector_PinHeader_2.54mm:PinHeader_1x04_P2.54mm_Vertical",
         pins={"1": "+3V3", "2": "GND", "3": "SDA", "4": "SCL"}, pos=(7.06, 47.86, 90), sch=(165.1, 162.56),
         mpn="Sensor-Kabel einloeten", labels=["VIN", "GND", "SDA", "SCL"]),
    dict(ref="J4", sym="Connector_Generic:Conn_01x05", value="Drehgeber",
         fp="Connector_PinHeader_2.54mm:PinHeader_1x05_P2.54mm_Vertical",
         pins={"1": "ENC_A", "2": "GND", "3": "ENC_B", "4": "ENC_SW", "5": "GND"}, pos=(19.76, 47.86, 90),
         sch=(203.2, 162.56), mpn="Drehgeber-Litzen einloeten", labels=["A", "C", "B", "SW", "GND"]),
]
for i, (c, r) in enumerate([(0, 0), (26, 0), (0, 18), (26, 18)]):
    PARTS.append(dict(ref="H%d" % (i + 1), sym="Mechanical:MountingHole", value="M2",
                      fp="MountingHole:MountingHole_2.2mm_M2", pins={}, grid={"": (c, r)},
                      sch=(248.92 + i * 12.7, 162.56), nobom=True))
for p in PARTS:
    p["smd"] = False       # nichts wird bestueckt

PWR_FLAGS = ["GND", "+V", "VDC"]
WIDTH = {"K8": 0.6, "+V": 0.6, "VDC": 0.6, "+5V": 0.6, "GND": 0.5, "+9V": 0.4}
DEFAULT_WIDTH = 0.3


def nets():
    s = set()
    for p in PARTS:
        for n in p["pins"].values():
            if n:
                s.add(n)
    return sorted(s)
